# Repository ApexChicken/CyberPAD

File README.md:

# CyberPAD

The CyberPAD is a 4-button macropad with a seeduino and cherry keycaps.

## Usage

Designed with simple plug-and-play utility in mind, the CyberPAD only requires a single program (code.py),and a USB-C cable. Configuration for using it can be done within the python program (I've added comments so that tech-knowledge is less required), or Powertoys on Windows 11. Beyond that, its yours to use!

## Why I Made This

I designed this macropad as my first project within PCB design, which is a topic I've been wanting to get into for quite some time. Using Hack Clubs step-by-step guide (with some alterations), I have designed my own macropad, which I plan to use as shortcuts when making CAD and PCB designs.

## Some cool pictures

# Parts List

| Component | Description | Link | Unit Price | Qty | Total |
|-----------|-------------|------|------------|-----|-------|
| XIAO RP2040 | Seeeduino controller | [Amazon](https://a.co/d/06JD7nHi) | $9.99 | 1 | $9.99 |
| MX Red Cherry Switches | Keys | [Amazon](https://a.co/d/0eW07bUH) | $8.99 | 1 | $18.98 |
| PCB | Electrical circuit | [PCBWAY](https://pcbway.com) | $5.53 | 1 | $24.54 |

**Total: $53.51**

Please note that quotes for PCBS in PCBWay require a minimum of five, as do many other sites.

## Cad OnShape Link
https://cad.onshape.com/documents/a1507f5f0e4eeb5644f69423/w/125d68dc38391eaa10046ff1/e/2616dcde7568e61b7653e984?renderMode=0&uiState=69b075079bff67079c8a8d95

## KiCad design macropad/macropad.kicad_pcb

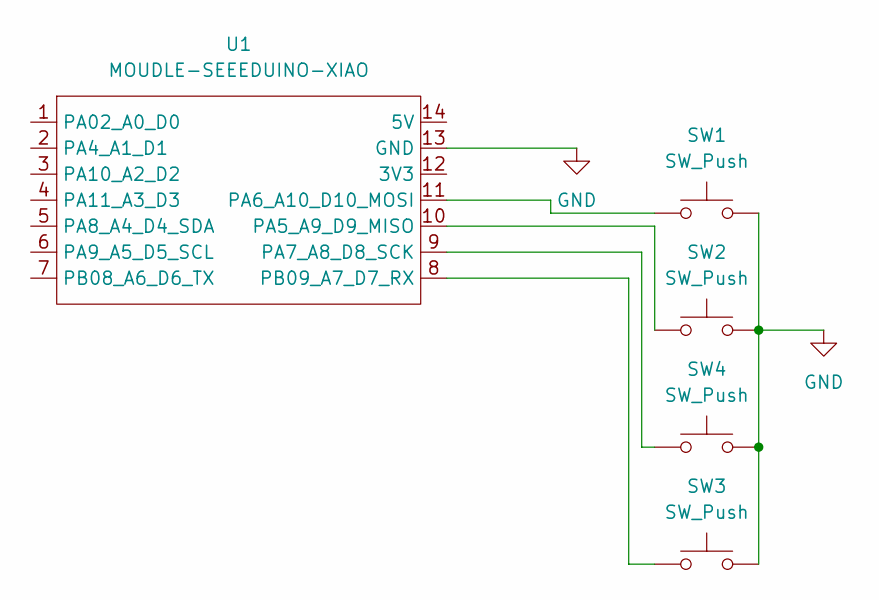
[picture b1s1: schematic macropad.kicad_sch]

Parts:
SW1, SW2, SW3, SW4: SW_Push; SW_Cherry_MX_1.00u_PCB
U1: MOUDLE-SEEEDUINO-XIAO; XIAO-Generic-Hybrid-14P-2.54-21X17.8MM

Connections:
GND: SW1.2, SW2.2, SW3.2, SW4.2, U1.13 (GND)
unnamed: SW2.1, U1.10 (PA5_A9_D9_MISO)
unnamed: SW1.1, U1.11 (PA6_A10_D10_MOSI)
unnamed: SW4.1, U1.9 (PA7_A8_D8_SCK)
unnamed: SW3.1, U1.8 (PB09_A7_D7_RX)

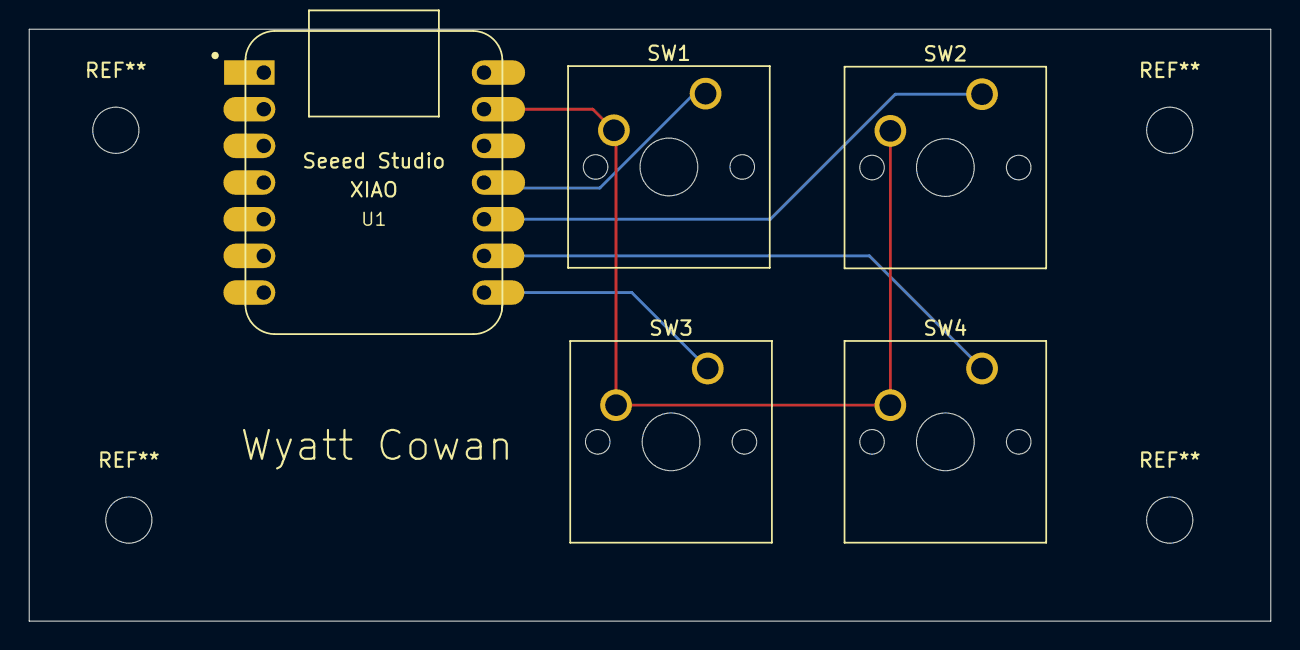
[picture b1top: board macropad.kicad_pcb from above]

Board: 2 copper layers, 86.0 x 41.0 mm, 5 parts (0 on the bottom side), 5 nets.

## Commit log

2026-03-05 Added STL Casing
2026-03-05 Added PCB files for CyberPAD
2026-03-05 Added KiCAD Care Package
    Just added in case of compatibility issues
2026-03-05 Revise README for 4-Button Macropad project
    Expanded project details and usage instructions.
2026-03-07 Enhance README with images and overview update
    Added images and updated overview description.
2026-03-07 Fix formatting issue in README overview section
2026-03-07 Rename project to CyberPAD and update README
    Updated the README to reflect the new name and usage instructions for the CyberPAD. Added itemized bill and images.
2026-03-10 Clean up itemized bill table formatting
    Removed separator lines from itemized bill table
2026-03-10 Fix formatting in itemized bill section of README
2026-03-10 Revise parts list and total cost in README
    Updated the parts list format and added total cost.
2026-03-10 Add OnShape link to README
2026-03-10 Added screenshot of PCB cost
2026-03-10 Rename Screenshot_20260310_182712.png to PCBcost
